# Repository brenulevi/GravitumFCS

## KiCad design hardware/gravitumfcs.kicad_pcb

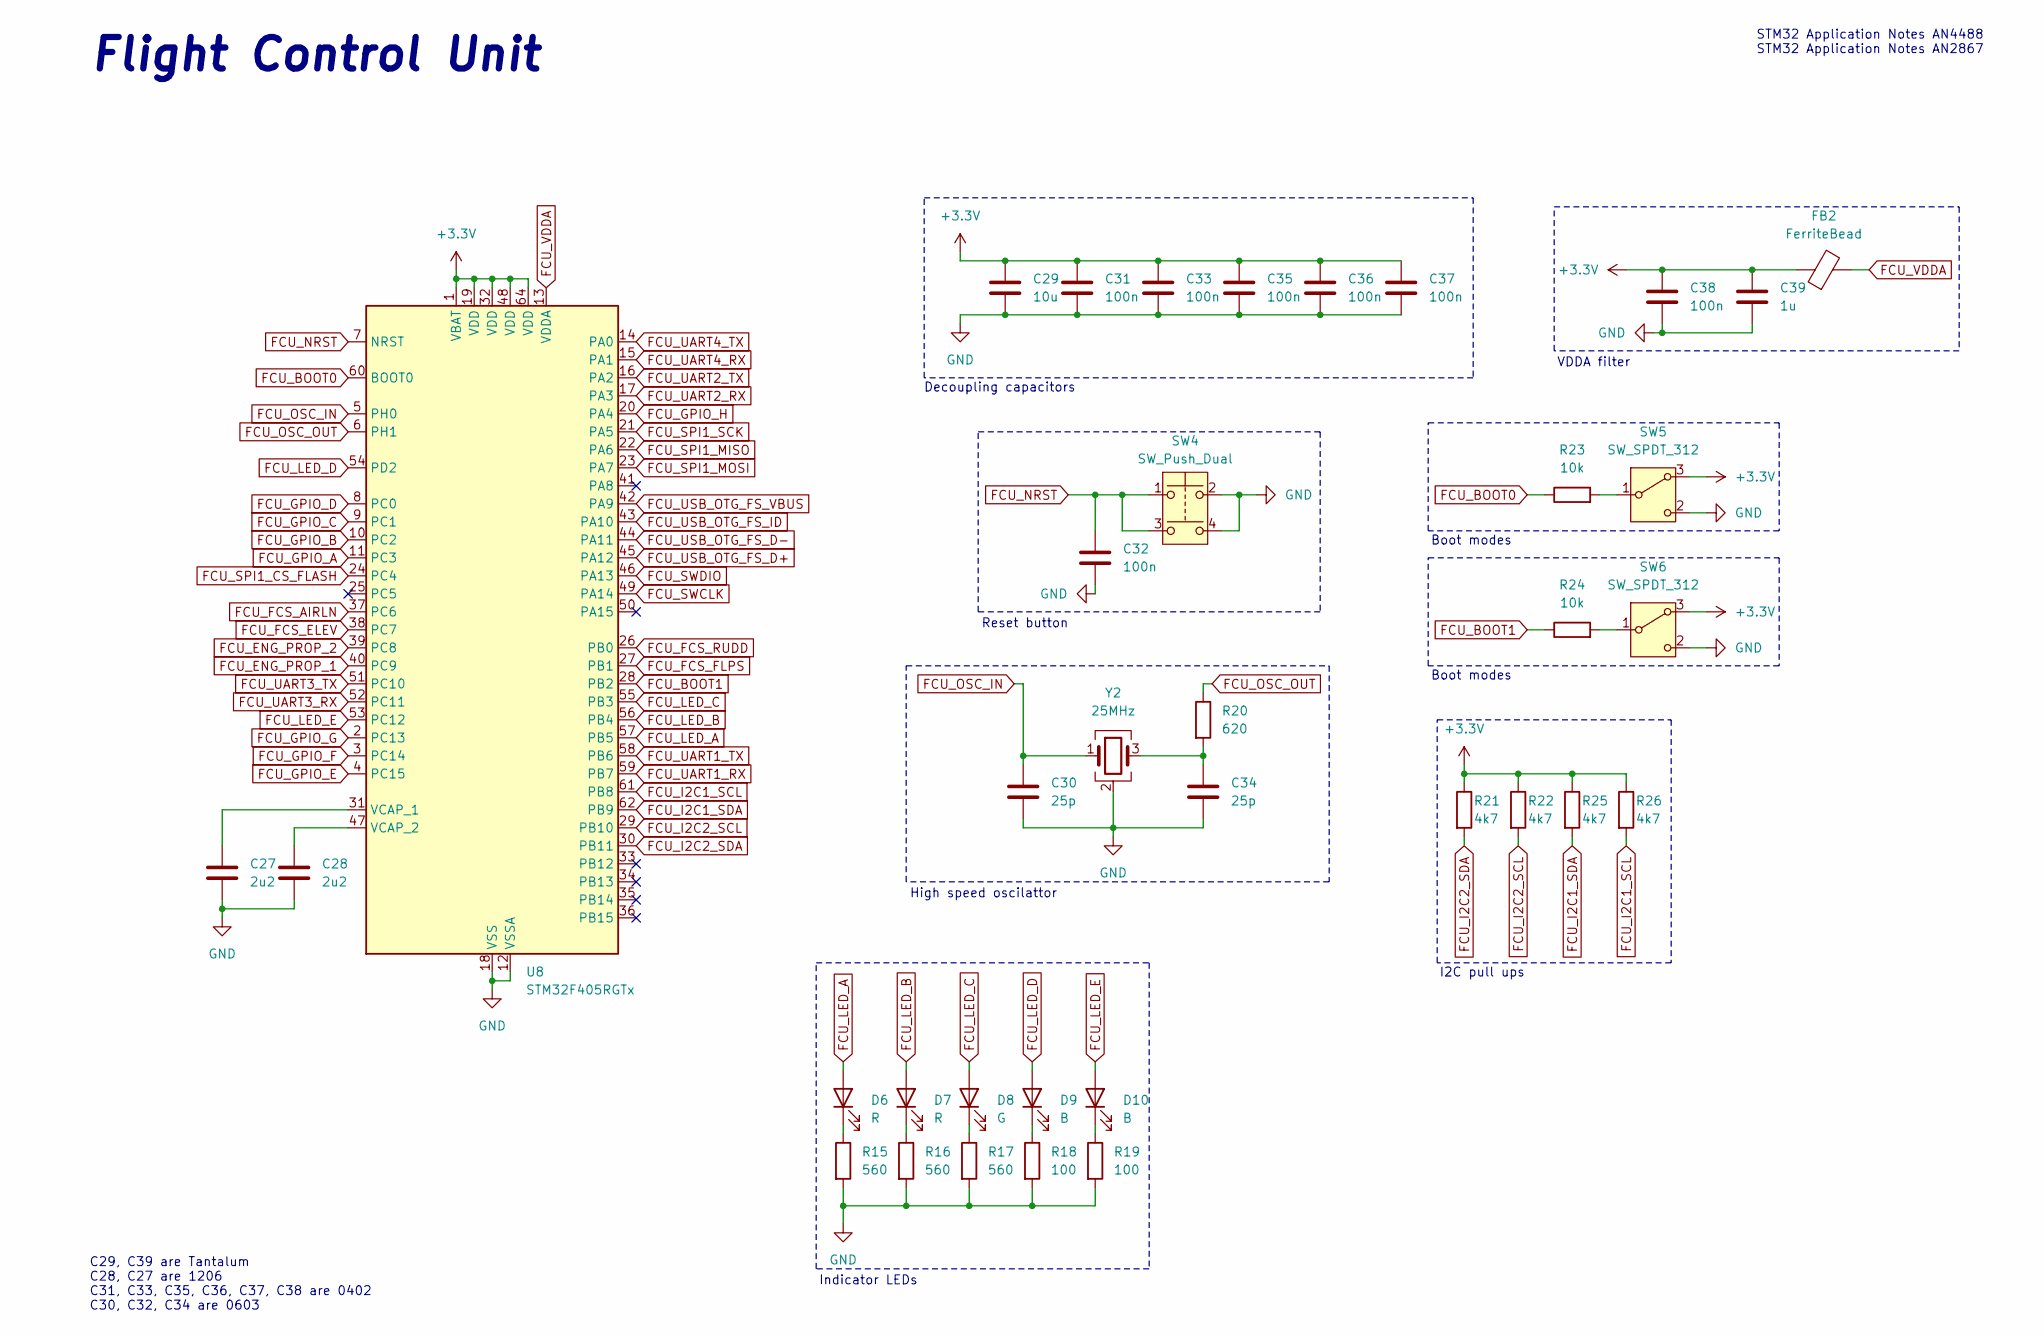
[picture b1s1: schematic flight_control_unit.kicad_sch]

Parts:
C27, C28: 2u2; C_0805_2012Metric
C29: 10u; C_0603_1608Metric
C30, C34: 25p; C_0603_1608Metric
C31, C32, C33, C35, C36, C37, C38: 100n; C_0402_1005Metric
C39: 1u; C_0603_1608Metric
D6, D7: R; LED_0603_1608Metric
D8: G; LED_0603_1608Metric
D9, D10: B; LED_0603_1608Metric
FB2: FerriteBead; L_0603_1608Metric
R15, R16, R17: 560; R_0603_1608Metric
R18, R19: 100; R_0603_1608Metric
R20: 620; R_0603_1608Metric
R21, R22, R25, R26: 4k7; R_0603_1608Metric
R23, R24: 10k; R_0603_1608Metric
SW4: SW_Push_Dual; SW_TL3365AF180QG; Manufacturer Part Number TL3365AF180QG
SW5, SW6: SW_SPDT_312; SW_SPDT_PCM12; Manufacturer Part Number PCM12SMTR
U8: STM32F405RGTx; LQFP-64_10x10mm_P0.5mm; Manufacturer Part Number STM32F405RGT6
Y2: 25MHz; XTAL_ABM8G-25.000MHZ-18-D2Y-T; Manufacturer Part Number ABM8G-25.000MHZ-18-D2Y-T

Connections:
+3.3V: C29.1, C31.1, C33.1, C35.1, C36.1, C37.1, C38.1, C39.1, FB2.1, R21.1, R22.1, R25.1, R26.1, SW5.3 (A), SW6.3 (A), U8.1 (VBAT), U8.19 (VDD), U8.32 (VDD), U8.48 (VDD), U8.64 (VDD); also elsewhere on the board
FCU_BOOT0: R23.1, U8.60 (BOOT0)
FCU_BOOT1: R24.1, U8.28 (PB2)
FCU_ENG_PROP_1: U8.40 (PC9); also elsewhere on the board
FCU_ENG_PROP_2: U8.39 (PC8); also elsewhere on the board
FCU_FCS_AIRLN: U8.37 (PC6); also elsewhere on the board
FCU_FCS_ELEV: U8.38 (PC7); also elsewhere on the board
FCU_FCS_FLPS: U8.27 (PB1); also elsewhere on the board
FCU_FCS_RUDD: U8.26 (PB0); also elsewhere on the board
FCU_GPIO_A: U8.11 (PC3); also elsewhere on the board
FCU_GPIO_B: U8.10 (PC2); also elsewhere on the board
FCU_GPIO_C: U8.9 (PC1); also elsewhere on the board
FCU_GPIO_D: U8.8 (PC0); also elsewhere on the board
FCU_GPIO_E: U8.4 (PC15); also elsewhere on the board
FCU_GPIO_F: U8.3 (PC14); also elsewhere on the board
FCU_GPIO_G: U8.2 (PC13); also elsewhere on the board
FCU_GPIO_H: U8.20 (PA4); also elsewhere on the board
FCU_I2C1_SCL: R26.2, U8.61 (PB8); also elsewhere on the board
FCU_I2C1_SDA: R25.2, U8.62 (PB9); also elsewhere on the board
FCU_I2C2_SCL: R22.2, U8.29 (PB10); also elsewhere on the board
FCU_I2C2_SDA: R21.2, U8.30 (PB11); also elsewhere on the board
FCU_LED_A: D6.2 (A), U8.57 (PB5)
FCU_LED_B: D7.2 (A), U8.56 (PB4)
FCU_LED_C: D8.2 (A), U8.55 (PB3)
FCU_LED_D: D9.2 (A), U8.54 (PD2)
FCU_LED_E: D10.2 (A), U8.53 (PC12)
FCU_NRST: C32.1, SW4.1, SW4.3, U8.7 (NRST); also elsewhere on the board
FCU_OSC_IN: C30.1, U8.5 (PH0), Y2.1
FCU_OSC_OUT: R20.1, U8.6 (PH1)
FCU_SPI1_CS_FLASH: U8.24 (PC4); also elsewhere on the board
FCU_SPI1_MISO: U8.22 (PA6); also elsewhere on the board
FCU_SPI1_MOSI: U8.23 (PA7); also elsewhere on the board
FCU_SPI1_SCK: U8.21 (PA5); also elsewhere on the board
FCU_SWCLK: U8.49 (PA14); also elsewhere on the board
FCU_SWDIO: U8.46 (PA13); also elsewhere on the board
FCU_UART1_RX: U8.59 (PB7); also elsewhere on the board
FCU_UART1_TX: U8.58 (PB6); also elsewhere on the board
FCU_UART2_RX: U8.17 (PA3); also elsewhere on the board
FCU_UART2_TX: U8.16 (PA2); also elsewhere on the board
FCU_UART3_RX: U8.52 (PC11); also elsewhere on the board
FCU_UART3_TX: U8.51 (PC10); also elsewhere on the board
FCU_UART4_RX: U8.15 (PA1); also elsewhere on the board
FCU_UART4_TX: U8.14 (PA0); also elsewhere on the board
FCU_USB_OTG_FS_D+: U8.45 (PA12); also elsewhere on the board
FCU_USB_OTG_FS_D-: U8.44 (PA11); also elsewhere on the board
FCU_USB_OTG_FS_ID: U8.43 (PA10); also elsewhere on the board
FCU_USB_OTG_FS_VBUS: U8.42 (PA9); also elsewhere on the board
FCU_VDDA: FB2.2, U8.13 (VDDA)
GND: C27.2, C28.2, C29.2, C30.2, C31.2, C32.2, C33.2, C34.2, C35.2, C36.2, C37.2, C38.2, C39.2, R15.2, R16.2, R17.2, R18.2, R19.2, SW4.2, SW4.4, SW5.2 (C), SW6.2 (C), U8.12 (VSSA), U8.18 (VSS), U8.63 (VSS), Y2.2 (G), Y2.4 (G); also elsewhere on the board
unnamed: C34.1, R20.2, Y2.3
unnamed: D6.1 (K), R15.1
unnamed: D7.1 (K), R16.1
unnamed: D8.1 (K), R17.1
unnamed: D9.1 (K), R18.1
unnamed: D10.1 (K), R19.1
unnamed: R23.2, SW5.1 (B)
unnamed: R24.2, SW6.1 (B)
unnamed: C27.1, U8.31 (VCAP_1)
unnamed: C28.1, U8.47 (VCAP_2)

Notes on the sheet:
High speed oscilattor
VDDA filter
Flight Control Unit
Boot modes
Indicator LEDs
Reset button
STM32 Application Notes AN4488 STM32 Application Notes AN2867
Decoupling capacitors
I2C pull ups
C29, C39 are Tantalum C28, C27 are 1206 C31, C33, C35, C36, C37, C38 are 0402 C30, C32, C34 are 0603

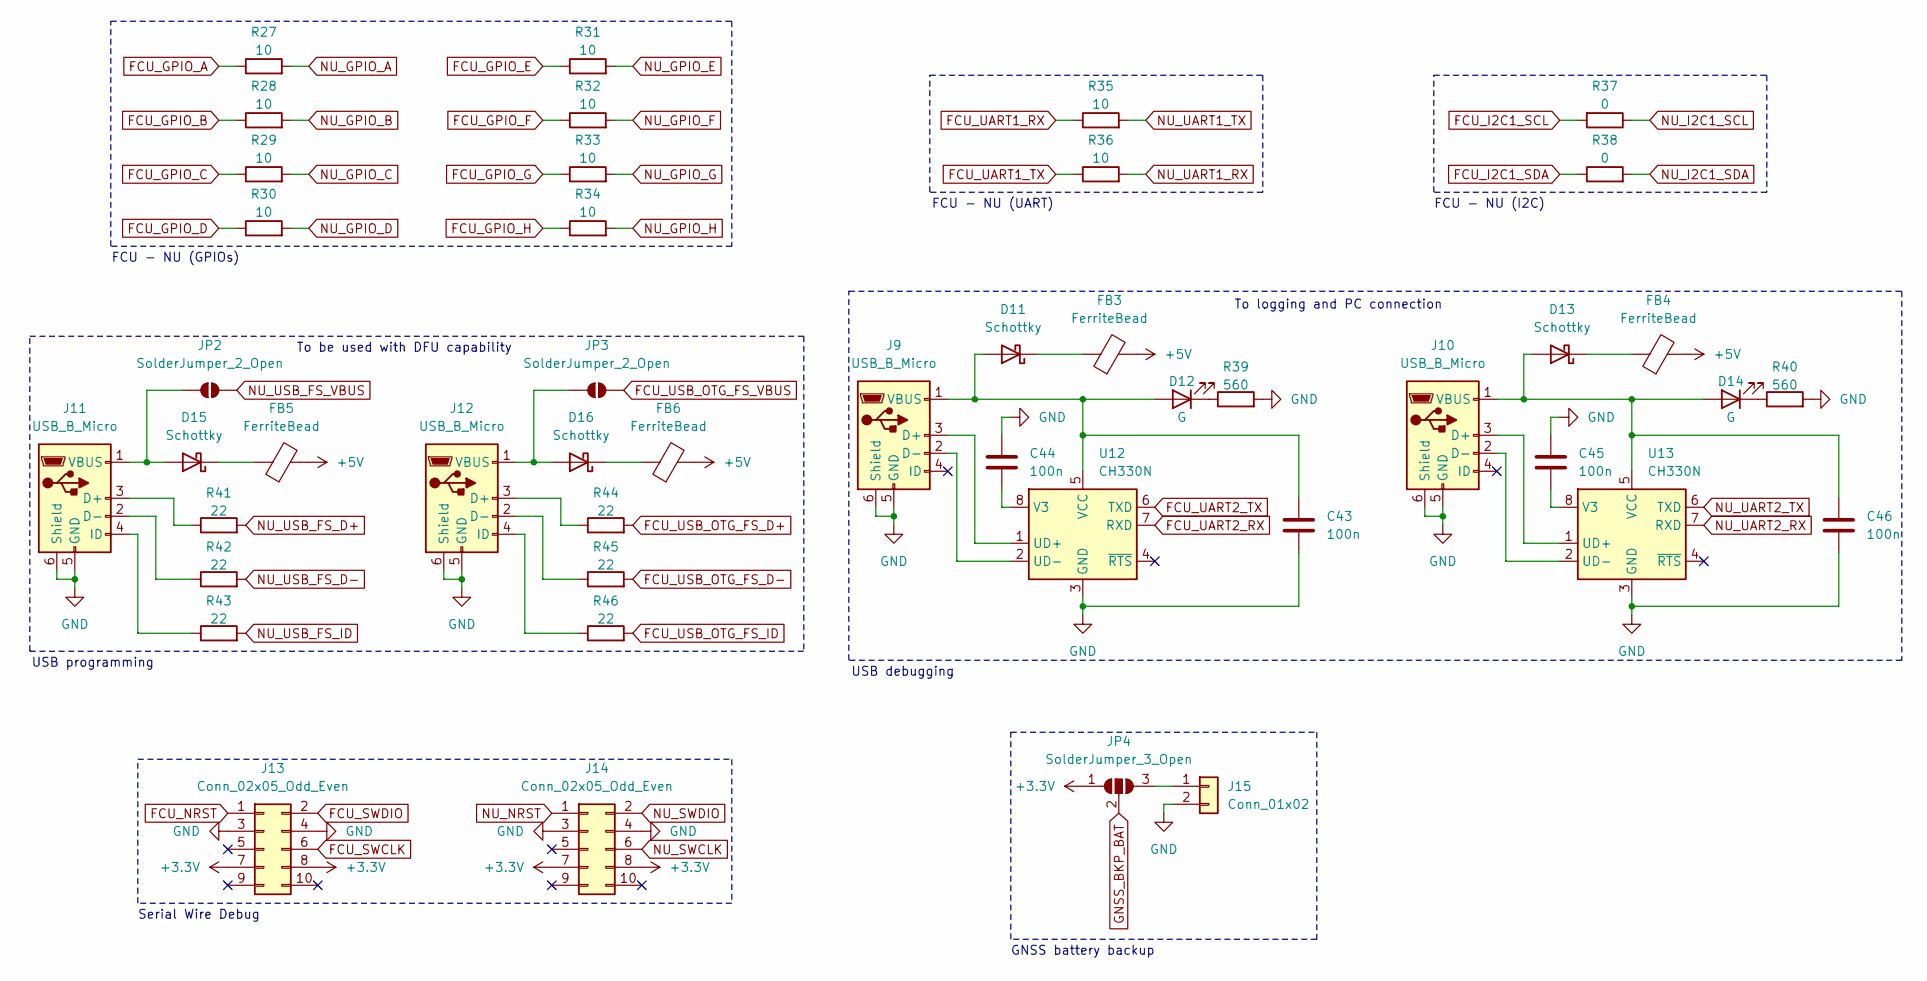
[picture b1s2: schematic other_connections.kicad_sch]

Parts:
C43, C44, C45, C46: 100n; C_0603_1608Metric
D11, D13, D15, D16: Schottky; SOD2713X115N
D12, D14: G; LED_0603_1608Metric
FB3, FB4, FB5, FB6: FerriteBead; L_0603_1608Metric
J9, J10, J11, J12: USB_B_Micro; USB_Micro-B_Molex_47346-0001; Manufacturer Part Number 0473461001
J13, J14: Conn_02x05_Odd_Even; JST_PHD_B10B-PHDSS_2x05_P2.00mm_Vertical; Manufacturer Part Number B10B-PHDSS
J15: Conn_01x02; JST_PH_S2B-PH-K_1x02_P2.00mm_Horizontal; Manufacturer Part Number S2B-PH-K-S
JP2, JP3: SolderJumper_2_Open; SolderJumper-2_P1.3mm_Open_RoundedPad1.0x1.5mm
JP4: SolderJumper_3_Open; SolderJumper-3_P1.3mm_Open_RoundedPad1.0x1.5mm
R27, R28, R29, R30, R31, R32, R33, R34, R35, R36: 10; R_0603_1608Metric
R37, R38: 0; R_0603_1608Metric
R39, R40: 560; R_0603_1608Metric
R41, R42, R43, R44, R45, R46: 22; R_0603_1608Metric
U12, U13: CH330N; SOIC-8_3.9x4.9mm_P1.27mm

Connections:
+3.3V: J13.7, J13.8, J14.7, J14.8, JP4.1 (A); also elsewhere on the board
+5V: FB3.2, FB4.2, FB5.2, FB6.2; also elsewhere on the board
FCU_GPIO_A: R27.1; also elsewhere on the board
FCU_GPIO_B: R28.1; also elsewhere on the board
FCU_GPIO_C: R29.1; also elsewhere on the board
FCU_GPIO_D: R30.1; also elsewhere on the board
FCU_GPIO_E: R31.1; also elsewhere on the board
FCU_GPIO_F: R32.1; also elsewhere on the board
FCU_GPIO_G: R33.1; also elsewhere on the board
FCU_GPIO_H: R34.1; also elsewhere on the board
FCU_I2C1_SCL: R37.2; also elsewhere on the board
FCU_I2C1_SDA: R38.1; also elsewhere on the board
FCU_NRST: J13.1; also elsewhere on the board
FCU_SWCLK: J13.6; also elsewhere on the board
FCU_SWDIO: J13.2; also elsewhere on the board
FCU_UART1_RX: R35.1; also elsewhere on the board
FCU_UART1_TX: R36.1; also elsewhere on the board
FCU_UART2_RX: U12.7 (RXD); also elsewhere on the board
FCU_UART2_TX: U12.6 (TXD); also elsewhere on the board
FCU_USB_OTG_FS_D+: R44.2; also elsewhere on the board
FCU_USB_OTG_FS_D-: R45.2; also elsewhere on the board
FCU_USB_OTG_FS_ID: R46.2; also elsewhere on the board
FCU_USB_OTG_FS_VBUS: JP3.2 (B); also elsewhere on the board
GND: C43.2, C44.1, C45.1, C46.2, J9.5 (GND), J9.6 (Shield), J10.5 (GND), J10.6 (Shield), J11.5 (GND), J11.6 (Shield), J12.5 (GND), J12.6 (Shield), J13.3, J13.4, J14.3, J14.4, J15.2, R39.2, R40.2, U12.3 (GND), U13.3 (GND); also elsewhere on the board
GNSS_BKP_BAT: JP4.2 (C); also elsewhere on the board
NU_GPIO_A: R27.2; also elsewhere on the board
NU_GPIO_B: R28.2; also elsewhere on the board
NU_GPIO_C: R29.2; also elsewhere on the board
NU_GPIO_D: R30.2; also elsewhere on the board
NU_GPIO_E: R31.2; also elsewhere on the board
NU_GPIO_F: R32.2; also elsewhere on the board
NU_GPIO_G: R33.2; also elsewhere on the board
NU_GPIO_H: R34.2; also elsewhere on the board
NU_I2C1_SCL: R37.1; also elsewhere on the board
NU_I2C1_SDA: R38.2; also elsewhere on the board
NU_NRST: J14.1; also elsewhere on the board
NU_SWCLK: J14.6; also elsewhere on the board
NU_SWDIO: J14.2; also elsewhere on the board
NU_UART1_RX: R36.2; also elsewhere on the board
NU_UART1_TX: R35.2; also elsewhere on the board
NU_UART2_RX: U13.7 (RXD); also elsewhere on the board
NU_UART2_TX: U13.6 (TXD); also elsewhere on the board
NU_USB_FS_D+: R41.2; also elsewhere on the board
NU_USB_FS_D-: R42.2; also elsewhere on the board
NU_USB_FS_ID: R43.2; also elsewhere on the board
NU_USB_FS_VBUS: JP2.2 (B); also elsewhere on the board
unnamed: C43.1, D11.2 (A), D12.2 (A), J9.1 (VBUS), U12.5 (VCC)
unnamed: D11.1 (K), FB3.1
unnamed: D12.1 (K), R39.1
unnamed: C46.1, D13.2 (A), D14.2 (A), J10.1 (VBUS), U13.5 (VCC)
unnamed: D13.1 (K), FB4.1
unnamed: D14.1 (K), R40.1
unnamed: D15.2 (A), J11.1 (VBUS), JP2.1 (A)
unnamed: D15.1 (K), FB5.1
unnamed: D16.2 (A), J12.1 (VBUS), JP3.1 (A)
unnamed: D16.1 (K), FB6.1
unnamed: J9.3 (D+), U12.1 (UD+)
unnamed: J9.2 (D-), U12.2 (UD-)
unnamed: J10.3 (D+), U13.1 (UD+)
unnamed: J10.2 (D-), U13.2 (UD-)
unnamed: J11.3 (D+), R41.1
unnamed: J11.2 (D-), R42.1
unnamed: J11.4 (ID), R43.1
unnamed: J12.3 (D+), R44.1
unnamed: J12.2 (D-), R45.1
unnamed: J12.4 (ID), R46.1
unnamed: J15.1, JP4.3 (B)
unnamed: C44.2, U12.8 (V3)
unnamed: C45.2, U13.8 (V3)

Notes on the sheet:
To be used with DFU capability
Serial Wire Debug
FCU - NU (I2C)
To logging and PC connection
GNSS battery backup
USB debugging
FCU - NU (GPIOs)
FCU - NU (UART)
USB programming

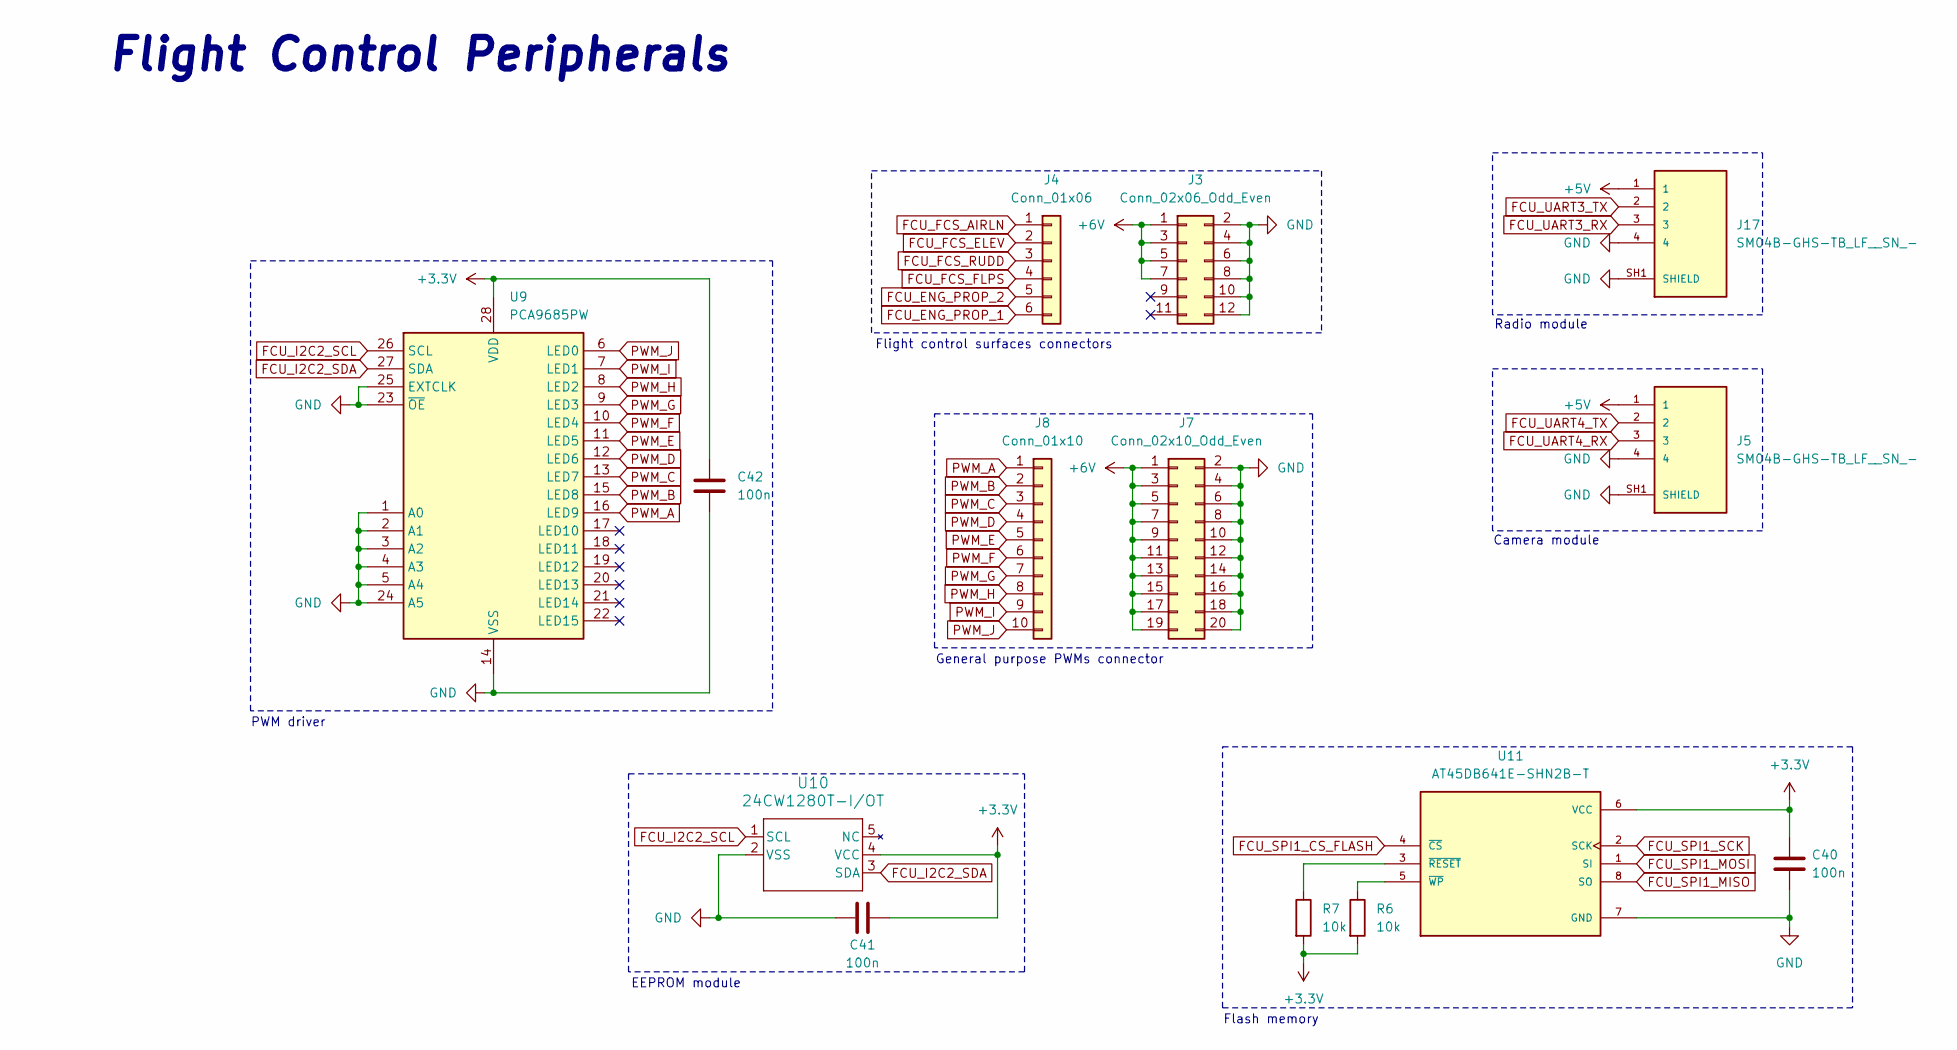
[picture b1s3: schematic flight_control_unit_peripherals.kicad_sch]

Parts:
C40, C41, C42: 100n; C_0603_1608Metric
J3: Conn_02x06_Odd_Even; PinHeader_2x06_P2.54mm_Vertical
J4: Conn_01x06; PinHeader_1x06_P2.54mm_Vertical
J5, J17: SM04B-GHS-TB_LF__SN_-; JST_SM04B-GHS-TB_LF__SN_-; PARTREV NA
J7: Conn_02x10_Odd_Even; PinHeader_2x10_P2.54mm_Vertical
J8: Conn_01x10; PinHeader_1x10_P2.54mm_Vertical
R6, R7: 10k; R_0603_1608Metric
U9: PCA9685PW; TSSOP-28_4.4x9.7mm_P0.65mm; Manufacturer Part Number PCA9685PW,118
U10: 24CW1280T-I/OT; SOT-23-5_2P9X1P6_MCH; Manufacturer Part Number 24CW1280T-I/OT
U11: AT45DB641E-SHN2B-T; SOIC127P798X216-8N; PARTREV DS-45DB641E-027K

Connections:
+3.3V: C40.1, C41.2, C42.1, R6.2, R7.2, U9.28 (VDD), U10.4 (VCC), U11.6 (VCC); also elsewhere on the board
+5V: J5.1, J17.1; also elsewhere on the board
+6V: J3.1, J3.3, J3.5, J3.7, J7.1, J7.3, J7.5, J7.7, J7.9, J7.11, J7.13, J7.15, J7.17, J7.19; also elsewhere on the board
FCU_ENG_PROP_1: J4.6; also elsewhere on the board
FCU_ENG_PROP_2: J4.5; also elsewhere on the board
FCU_FCS_AIRLN: J4.1; also elsewhere on the board
FCU_FCS_ELEV: J4.2; also elsewhere on the board
FCU_FCS_FLPS: J4.4; also elsewhere on the board
FCU_FCS_RUDD: J4.3; also elsewhere on the board
FCU_I2C2_SCL: U9.26 (SCL), U10.1 (SCL); also elsewhere on the board
FCU_I2C2_SDA: U9.27 (SDA), U10.3 (SDA); also elsewhere on the board
FCU_SPI1_CS_FLASH: U11.4 (~CS); also elsewhere on the board
FCU_SPI1_MISO: U11.8 (SO); also elsewhere on the board
FCU_SPI1_MOSI: U11.1 (SI); also elsewhere on the board
FCU_SPI1_SCK: U11.2 (SCK); also elsewhere on the board
FCU_UART3_RX: J17.3; also elsewhere on the board
FCU_UART3_TX: J17.2; also elsewhere on the board
FCU_UART4_RX: J5.3; also elsewhere on the board
FCU_UART4_TX: J5.2; also elsewhere on the board
GND: C40.2, C41.1, C42.2, J3.2, J3.4, J3.6, J3.8, J3.10, J3.12, J5.4, J5.SH1 (SHIELD), J5.SH2 (SHIELD), J7.2, J7.4, J7.6, J7.8, J7.10, J7.12, J7.14, J7.16, J7.18, J7.20, J17.4, J17.SH1 (SHIELD), J17.SH2 (SHIELD), U9.1 (A0), U9.2 (A1), U9.3 (A2), U9.4 (A3), U9.5 (A4), U9.14 (VSS), U9.23 (~OE), U9.24 (A5), U9.25 (EXTCLK), U10.2 (VSS), U11.7 (GND); also elsewhere on the board
unnamed: R7.1, U11.3 (~RESET)
unnamed: R6.1, U11.5 (~WP)
PWM_A: J8.1, U9.16 (LED9)
PWM_B: J8.2, U9.15 (LED8)
PWM_C: J8.3, U9.13 (LED7)
PWM_D: J8.4, U9.12 (LED6)
PWM_E: J8.5, U9.11 (LED5)
PWM_F: J8.6, U9.10 (LED4)
PWM_G: J8.7, U9.9 (LED3)
PWM_H: J8.8, U9.8 (LED2)
PWM_I: J8.9, U9.7 (LED1)
PWM_J: J8.10, U9.6 (LED0)

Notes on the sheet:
PWM driver
Flash memory
EEPROM module
Flight Control Peripherals
Radio module
General purpose PWMs connector
Flight control surfaces connectors
Camera module

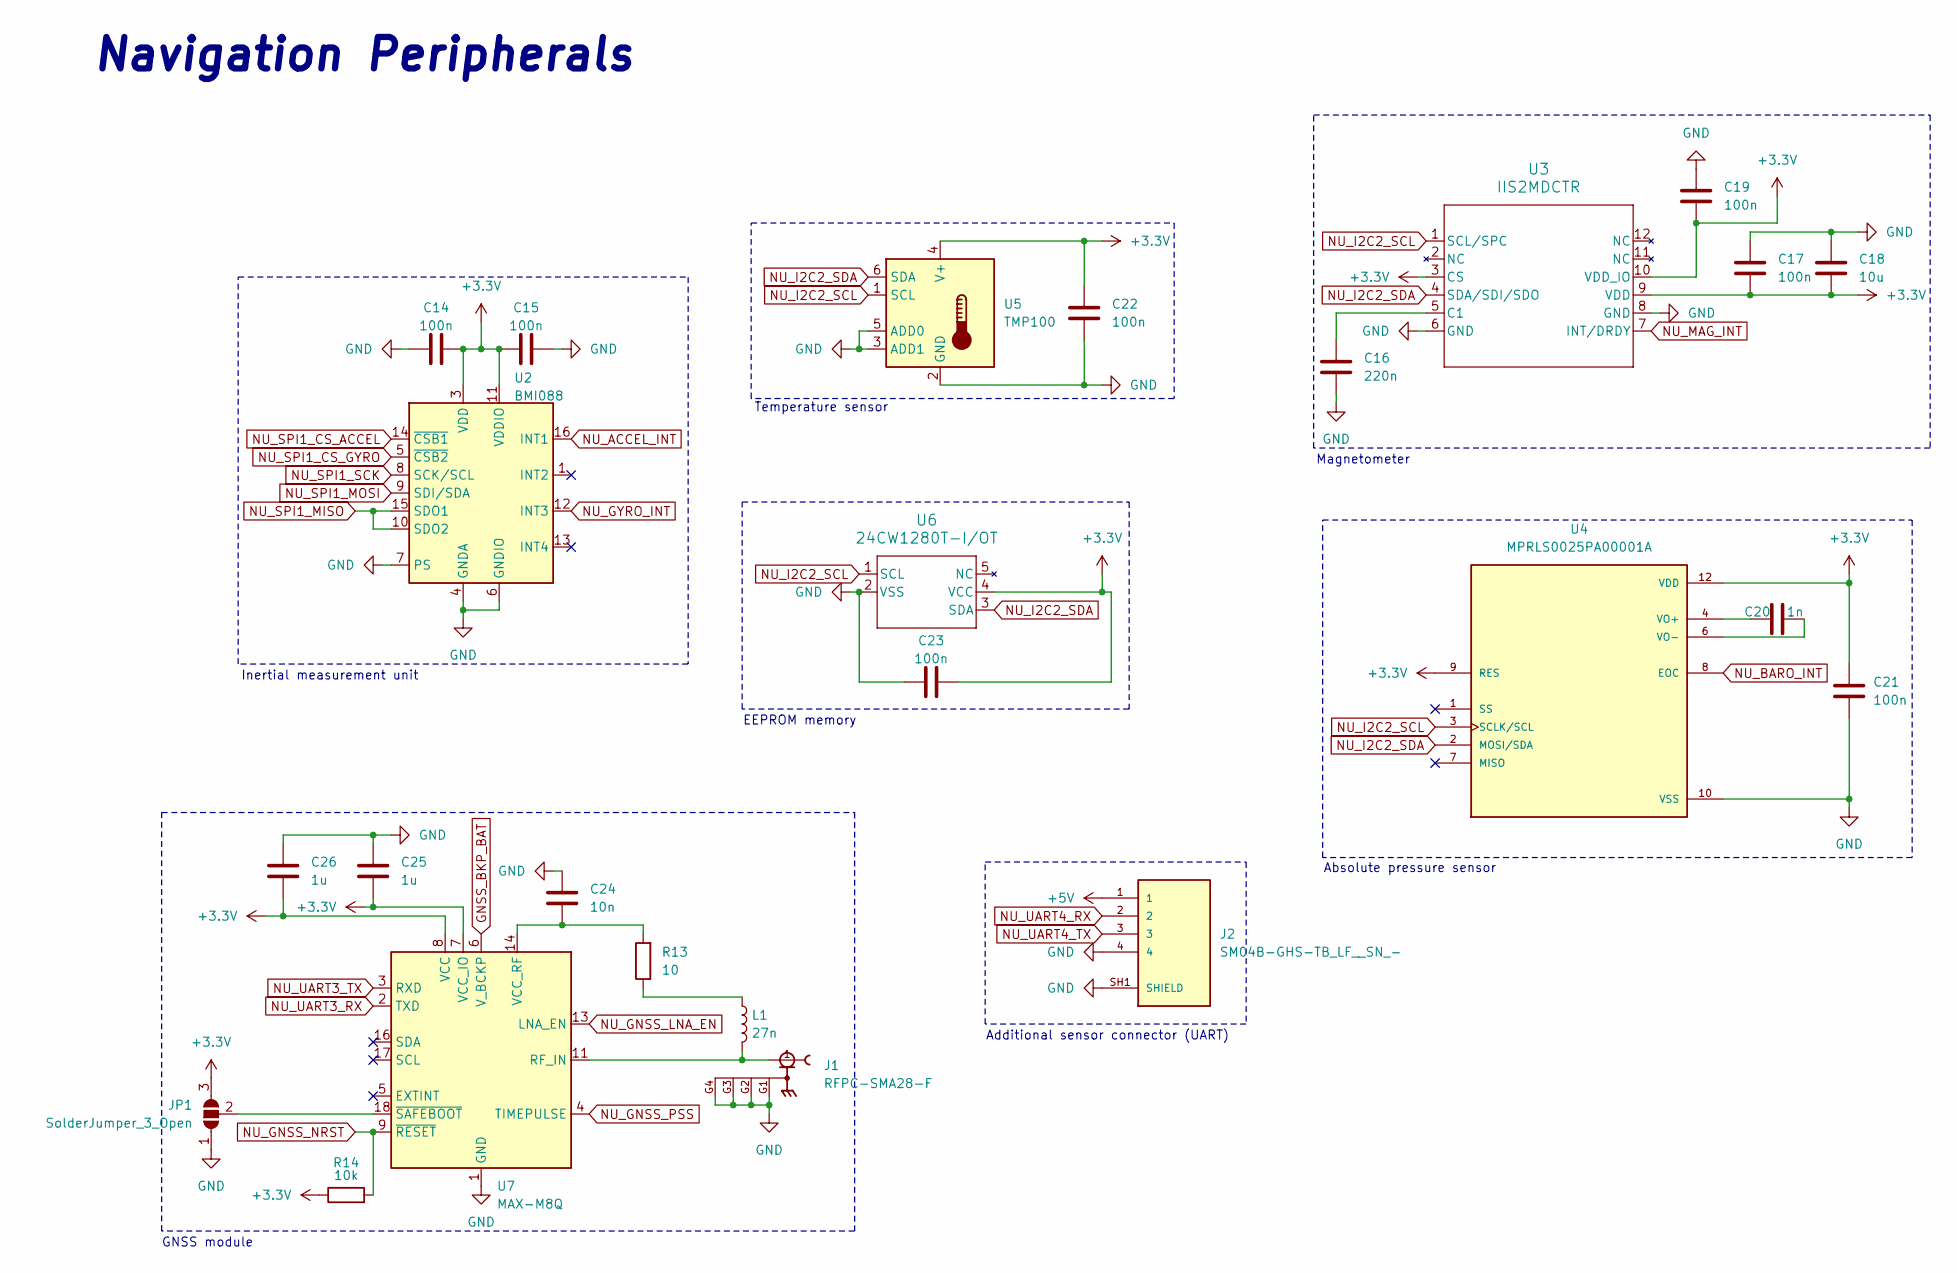
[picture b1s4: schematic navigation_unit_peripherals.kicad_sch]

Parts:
C14, C15, C17, C19, C21, C22, C23: 100n; C_0603_1608Metric
C16: 220n; C_0603_1608Metric
C18: 10u; C_0805_2012Metric
C20: 1n; C_0603_1608Metric
C24: 10n; C_0603_1608Metric
C25, C26: 1u; C_0603_1608Metric
J1: RFPC-SMA28-F; GRADCONN_RFPC-SMA28-F; PARTREV 1.0
J2: SM04B-GHS-TB_LF__SN_-; JST_SM04B-GHS-TB_LF__SN_-; PARTREV NA
JP1: SolderJumper_3_Open; SolderJumper-3_P1.3mm_Open_RoundedPad1.0x1.5mm
L1: 27n; L_0603_1608Metric
R13: 10; R_0603_1608Metric
R14: 10k; R_0603_1608Metric
U2: BMI088; Bosch_LGA-16_4.5x3mm_P0.5mm_LayoutBorder7x1y_ClockwisePinNu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; Manufacturer Part Number BMI088
U3: IIS2MDCTR; LGA-12_2X2X0P7_STM; Manufacturer Part Number IIS2MDCTR
U4: MPRLS0025PA00001A; XDCR_MPRLS0025PA00001A; PARTREV 03/18
U5: TMP100; SOT-23-6; Manufacturer Part Number TMP100NA/3K
U6: 24CW1280T-I/OT; SOT-23-5_2P9X1P6_MCH; Manufacturer Part Number 24CW1280T-I/OT
U7: MAX-M8Q; ublox_MAX; Manufacturer Part Number MAX-M8Q

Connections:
+3.3V: C14.2, C15.1, C17.2, C18.2, C19.2, C21.1, C22.1, C23.2, C25.2, C26.2, JP1.3 (B), R14.1, U2.3 (VDD), U2.11 (VDDIO), U3.3 (CS), U3.9 (VDD), U3.10 (VDD_IO), U4.9 (RES), U4.12 (VDD), U5.4 (V+), U6.4 (VCC), U7.7 (VCC_IO), U7.8 (VCC); also elsewhere on the board
+5V: J2.1; also elsewhere on the board
GND: C14.1, C15.2, C16.2, C17.1, C18.1, C19.1, C21.2, C22.2, C23.1, C24.1, C25.1, C26.1, J1.G1, J1.G2, J1.G3, J1.G4, J2.4, J2.SH1 (SHIELD), J2.SH2 (SHIELD), JP1.1 (A), U2.2 (GNDA), U2.4 (GNDA), U2.6 (GNDIO), U2.7 (PS), U3.6 (GND), U3.8 (GND), U4.10 (VSS), U5.2 (GND), U5.3 (ADD1), U5.5 (ADD0), U6.2 (VSS), U7.1 (GND), U7.10 (GND), U7.12 (GND); also elsewhere on the board
GNSS_BKP_BAT: U7.6 (V_BCKP); also elsewhere on the board
NU_ACCEL_INT: U2.16 (INT1); also elsewhere on the board
NU_BARO_INT: U4.8 (EOC); also elsewhere on the board
NU_GNSS_LNA_EN: U7.13 (LNA_EN); also elsewhere on the board
NU_GNSS_NRST: R14.2, U7.9 (~RESET); also elsewhere on the board
NU_GNSS_PSS: U7.4 (TIMEPULSE); also elsewhere on the board
NU_GYRO_INT: U2.12 (INT3); also elsewhere on the board
NU_I2C2_SCL: U3.1 (SCL/SPC), U4.3 (SCLK/SCL), U5.1 (SCL), U6.1 (SCL); also elsewhere on the board
NU_I2C2_SDA: U3.4 (SDA/SDI/SDO), U4.2 (MOSI/SDA), U5.6 (SDA), U6.3 (SDA); also elsewhere on the board
NU_MAG_INT: U3.7 (INT/DRDY); also elsewhere on the board
NU_SPI1_CS_ACCEL: U2.14 (~CSB1); also elsewhere on the board
NU_SPI1_CS_GYRO: U2.5 (~CSB2); also elsewhere on the board
NU_SPI1_MISO: U2.10 (SDO2), U2.15 (SDO1); also elsewhere on the board
NU_SPI1_MOSI: U2.9 (SDI/SDA); also elsewhere on the board
NU_SPI1_SCK: U2.8 (SCK/SCL); also elsewhere on the board
NU_UART3_RX: U7.2 (TXD); also elsewhere on the board
NU_UART3_TX: U7.3 (RXD); also elsewhere on the board
NU_UART4_RX: J2.2; also elsewhere on the board
NU_UART4_TX: J2.3; also elsewhere on the board
unnamed: JP1.2 (C), U7.18 (~SAFEBOOT)
unnamed: L1.1, R13.1
unnamed: C16.1, U3.5 (C1)
unnamed: C20.1, U4.4 (VO+)
unnamed: C20.2, U4.6 (VO-)
unnamed: J1.1, L1.2, U7.11 (RF_IN)
unnamed: C24.2, R13.2, U7.14 (VCC_RF)

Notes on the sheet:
GNSS module
Navigation Peripherals
Temperature sensor
Magnetometer
Inertial measurement unit
Additional sensor connector (UART)
Absolute pressure sensor
EEPROM memory

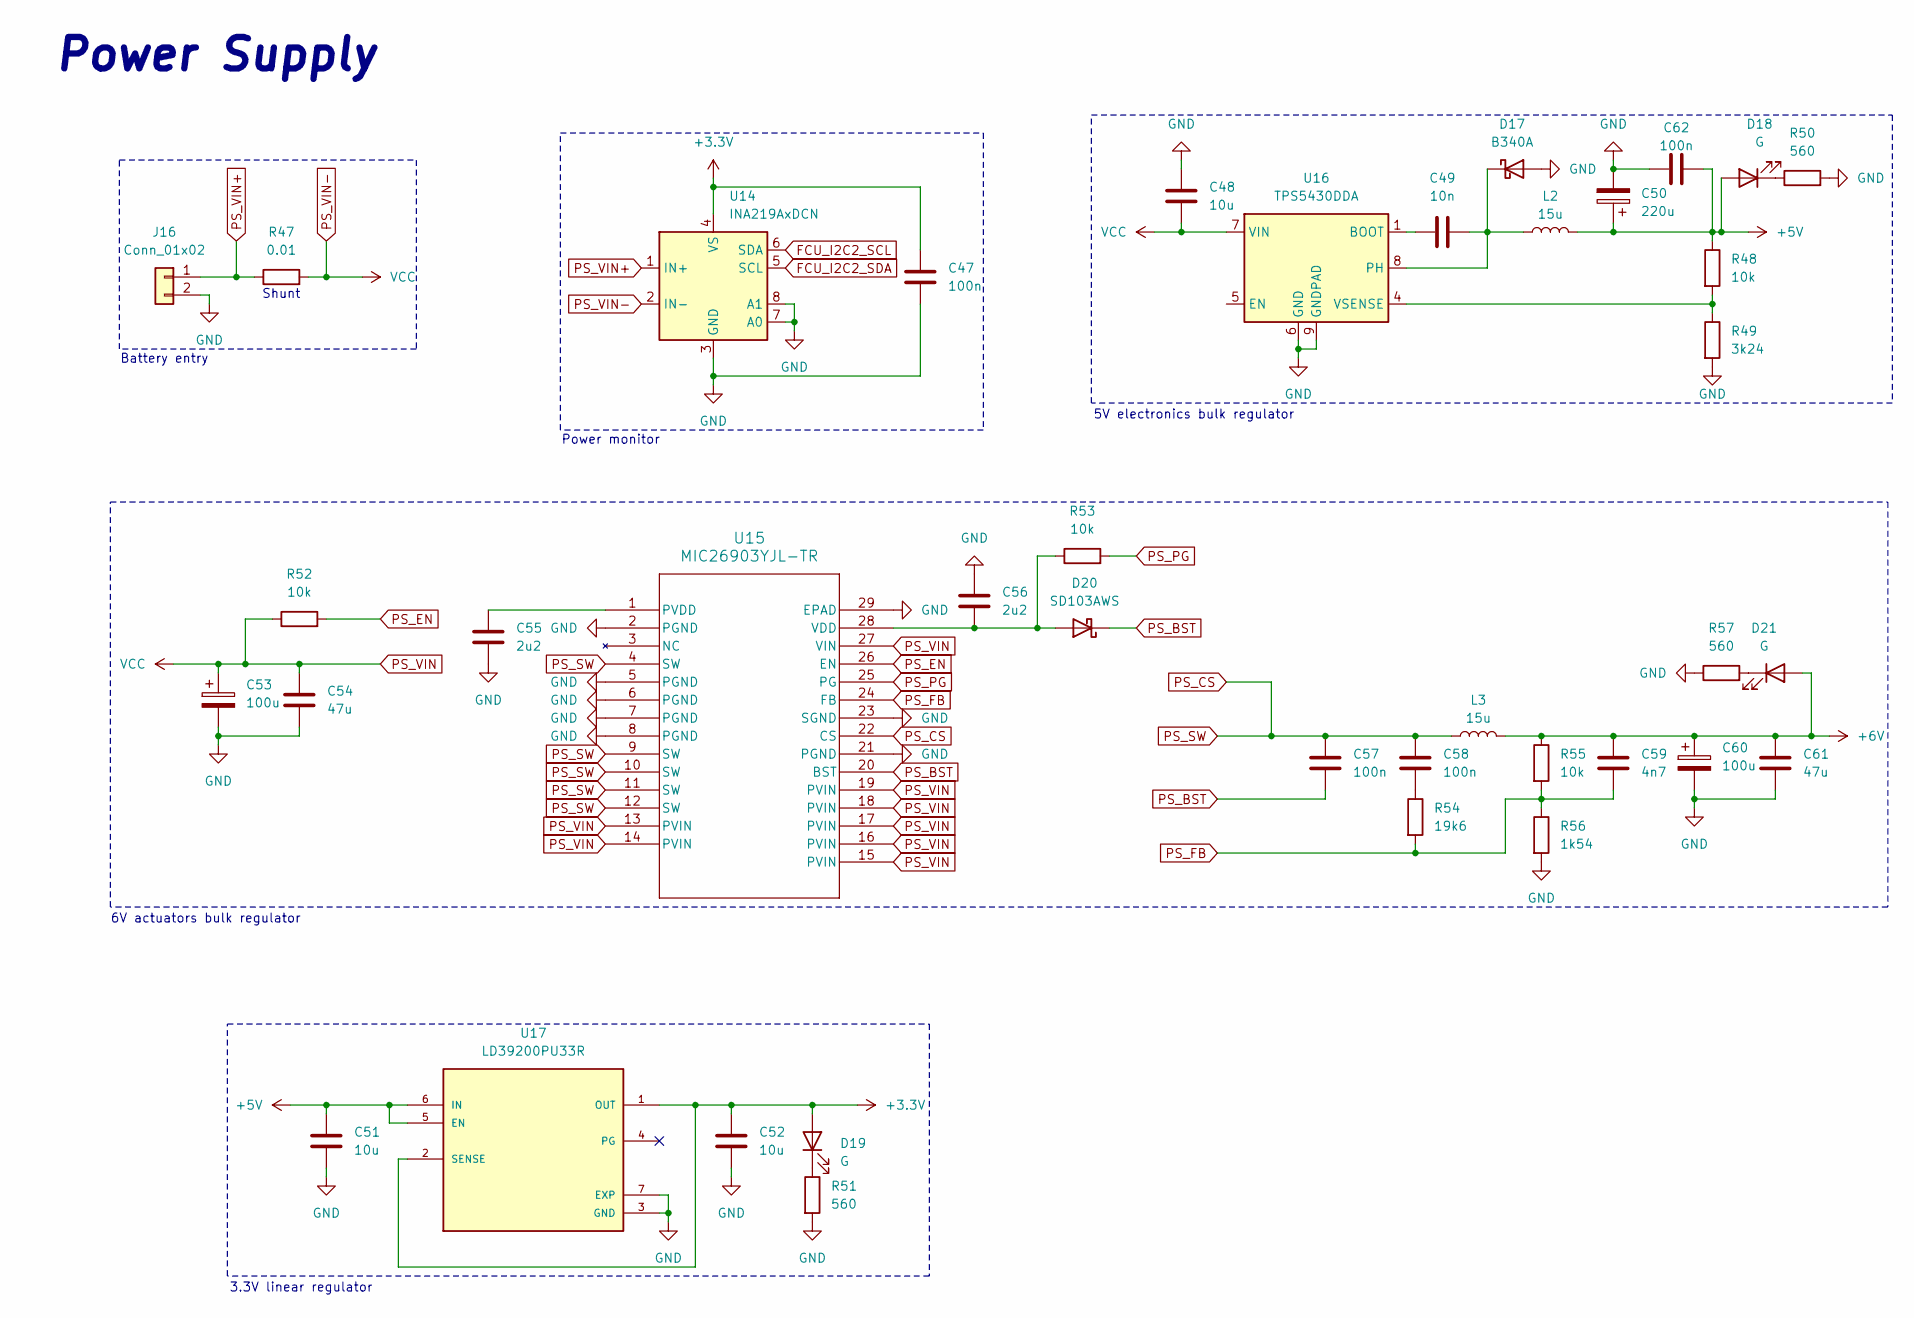
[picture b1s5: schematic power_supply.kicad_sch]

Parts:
C47, C57, C58, C62: 100n; C_0603_1608Metric
C48, C51, C52: 10u; C_1206_3216Metric
C49: 10n; C_0603_1608Metric
C50: 220u; CP_Elec_8x10
C53, C60: 100u; CP_Elec_8x10
C54, C61: 47u; C_1206_3216Metric
C55, C56: 2u2; C_0603_1608Metric
C59: 4n7; C_0603_1608Metric
D17: B340A; DIOM5226X240N; Manufacturer Part Number B340AE-13
D18, D19, D21: G; LED_0603_1608Metric
D20: SD103AWS; SOD2713X115N; Manufacturer Part Number SD103AWS
J16: Conn_01x02; AMASS_XT60-M_1x02_P7.20mm_Vertical; Manufacturer Part Number FIT0587
L2: 15u; L_APV_APH0615
L3: 15u; L_APV_APH1030
R47: 0.01; R_2512_6332Metric
R48, R52, R53, R55: 10k; R_0603_1608Metric
R49: 3k24; R_0603_1608Metric
R50, R51, R57: 560; R_0603_1608Metric
R54: 19k6; R_0603_1608Metric
R56: 1k54; R_0603_1608Metric
U14: INA219AxDCN; SOT-23-8; Manufacturer Part Number INA219AIDCNR
U15: MIC26903YJL-TR; CONV_MIC28510YJL-TR; Manufacturer Part Number MIC26903YJL-TR
U16: TPS5430DDA; TI_SO-PowerPAD-8_ThermalVias; Manufacturer Part Number TPS5430DDA
U17: LD39200PU33R; SON95P300X300X100-7N; PARTREV 3; DigiKey_Part_Number 497-15229-1-ND

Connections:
+3.3V: C47.1, C52.1, D19.2 (A), U14.4 (VS), U17.1 (OUT), U17.2 (SENSE); also elsewhere on the board
+5V: C50.1, C51.1, C62.1, D18.2 (A), L2.2, R48.1, U17.5 (EN), U17.6 (IN); also elsewhere on the board
+6V: C59.1, C60.1, C61.1, D21.2 (A), L3.2, R55.1; also elsewhere on the board
FCU_I2C2_SCL: U14.6 (SDA); also elsewhere on the board
FCU_I2C2_SDA: U14.5 (SCL); also elsewhere on the board
GND: C47.2, C48.1, C50.2, C51.2, C52.2, C53.2, C54.2, C55.2, C56.1, C60.2, C61.2, C62.2, D17.2 (A), J16.2, R49.2, R50.2, R51.2, R56.2, R57.1, U14.3 (GND), U14.7 (A0), U14.8 (A1), U15.2 (PGND), U15.5 (PGND), U15.6 (PGND), U15.7 (PGND), U15.8 (PGND), U15.21 (PGND), U15.23 (SGND), U15.29 (EPAD), U16.6 (GND), U16.9 (GNDPAD), U17.3 (GND), U17.7 (EXP); also elsewhere on the board
unnamed: C58.2, R54.1
unnamed: C49.2, D17.1 (K), L2.1, U16.8 (PH)
unnamed: D18.1 (K), R50.1
unnamed: D19.1 (K), R51.1
unnamed: C56.2, D20.2 (A), R53.1, U15.28 (VDD)
unnamed: D21.1 (K), R57.2
unnamed: C55.1, U15.1 (PVDD)
unnamed: C49.1, U16.1 (BOOT)
unnamed: R48.2, R49.1, U16.4 (VSENSE)
PS_BST: C57.2, D20.1 (K), U15.20 (BST)
PS_CS: C57.1, C58.1, L3.1, U15.4 (SW), U15.9 (SW), U15.10 (SW), U15.11 (SW), U15.12 (SW), U15.22 (CS)
PS_EN: R52.2, U15.26 (EN)
PS_FB: C59.2, R54.2, R55.2, R56.1, U15.24 (FB)
PS_PG: R53.2, U15.25 (PG)
PS_VIN: C48.2, C53.1, C54.1, R47.2, R52.1, U14.2 (IN-), U15.13 (PVIN), U15.14 (PVIN), U15.15 (PVIN), U15.16 (PVIN), U15.17 (PVIN), U15.18 (PVIN), U15.19 (PVIN), U15.27 (VIN), U16.7 (VIN)
PS_VIN+: J16.1, R47.1, U14.1 (IN+)

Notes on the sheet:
Shunt
Battery entry
6V actuators bulk regulator
5V electronics bulk regulator
Power monitor
3.3V linear regulator
Power Supply
